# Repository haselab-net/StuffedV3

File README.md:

# Stuffed toy robot version 3 (Starts from 2017) 

* This repository contains Motor driver boards'schematics / PCB layouts, their firmwares and PC software.
* See the wiki (http://git.haselab.net/hasevr/StuffedV3/wikis/home) also.

## Folder structure
- __PIC__ Firmware for pic. WROOM with motor driver also use part of this code.
- __WROOM__ Firmware for WROOM.
- __PCRobokey__ Windows software to control the robot.

# Architecture
WROOM: The main board. One robot has one board.
PIC: Motor driver extension board. Upto eight PIC boards share one UART to communicate with the main WROOM board.

# PIC
## Compiler
MPLABXIDE and XC32 compiler are needed. Install latest of both. Free vesion is enough.
- http://www.microchip.com/mplab/mplab-x-ide see download tab
- http://www.microchip.com/mplab/compilers see download tab

## Setting Macros in the source code.
There are some kinds of boards using the same firmware. So please define appropriate macro for your board.
 See __PIC/boardType.h__ and choose appropriate macro.
In addition, each board sharing the same UART should have different IDs. The ID must be 0 to 7.

# WROOM
 Haoyan Li made a development environment and tutorial.
 See https://github.com/VirgiliaBeatrice/esp32-devenv-vscode and install it.

# PCRobokey
Visual Studio 2015 (14) is used to build. Newer will also work.

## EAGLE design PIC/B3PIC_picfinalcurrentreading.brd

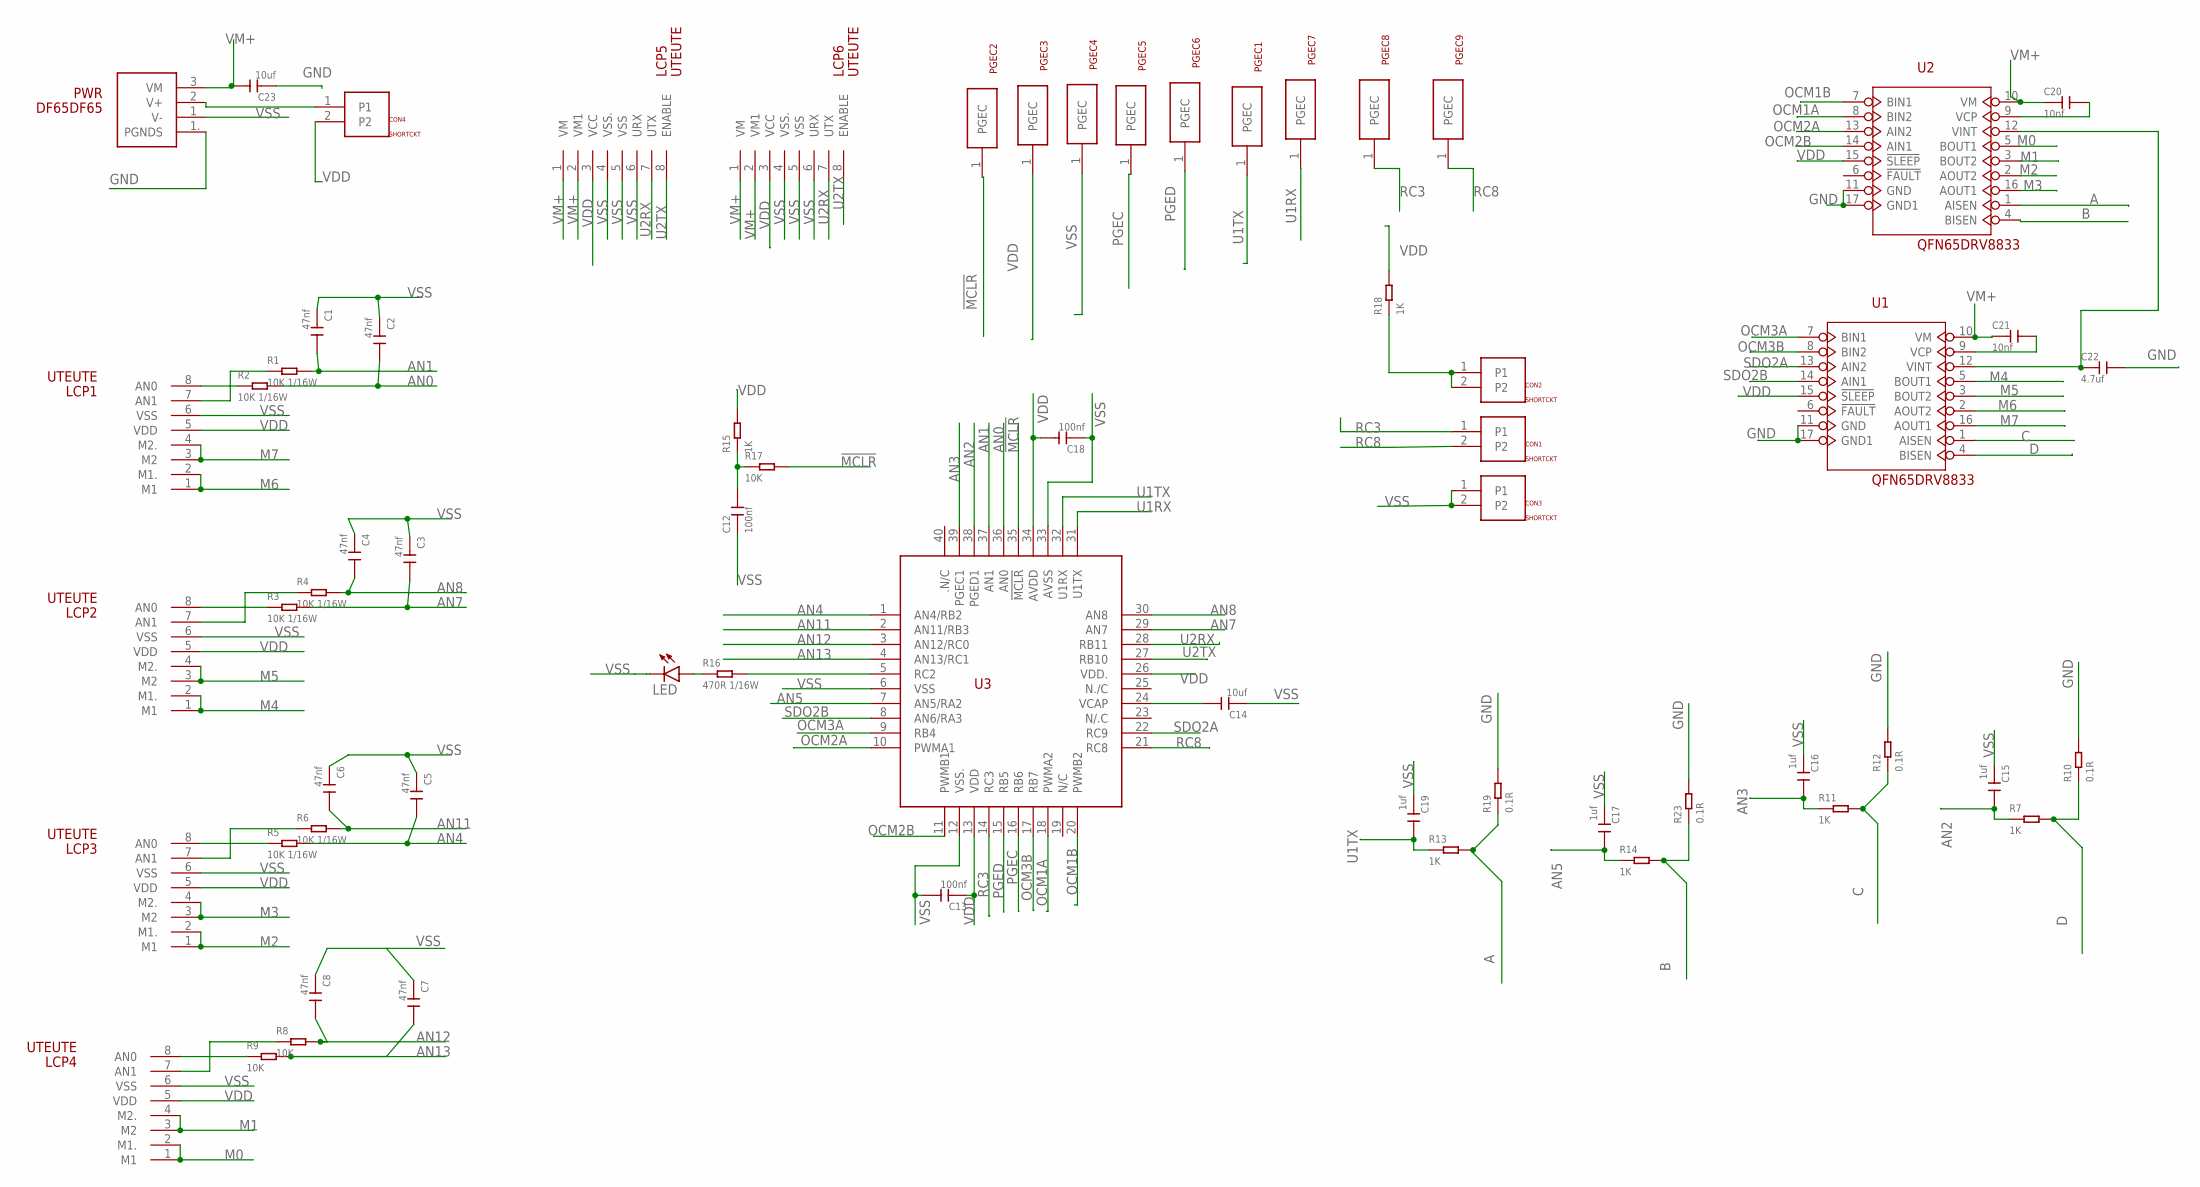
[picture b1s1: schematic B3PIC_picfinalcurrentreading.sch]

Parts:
C1, C2, C3, C4, C5, C6, C7, C8: 47nf; C0402
C12, C13, C18: 100nf; C0402
C14, C23: 10uf; C0402
C15, C16, C17, C19: 1uf; C0402
C20, C21: 10nf; C0402
C22: 4.7uf; C0402
CON1, CON2, CON3, CON4: SHORTCKT; SHORT
LCP1, LCP2, LCP3, LCP4, LCP5, LCP6: UTEUTE; UTE
LED: LEDCHIP-LED0603; CHIP-LED0603
PGEC1, PGEC2, PGEC3, PGEC4, PGEC5, PGEC6, PGEC7, PGEC8, PGEC9: PGECPGEC; PGEC
PWR: DF65DF65; DF65
R1, R2, R3, R4, R5, R6: 10K 1/16W; R0402
R7, R11, R13, R14, R15, R18: 1K; R0402
R8, R9, R17: 10K; R0402
R10, R12, R19, R23: 0.1R; R0805
R16: 470R 1/16W; R0402
U1, U2: QFN65DRV8833; QFN65P400X400X80-17N
U3: PIC32MM0064GPL036PIC32MM0064GPL36; UQFN40MV5X5MM

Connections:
!MCLR!: PGEC2.1, R17.2, U3.35 (!MCLR!)
A: R13.2, R19.1, U2.1 (AISEN)
AN0: C2.2, R2.2, U3.36 (AN0)
AN1: C1.2, R1.2, U3.37 (AN1)
AN2: C15.2, R7.1, U3.38 (PGED1)
AN3: C16.2, R11.1, U3.39 (PGEC1)
AN4: C5.2, R5.2, U3.1 (AN4/RB2)
AN5: C17.2, R14.1, U3.7 (AN5/RA2)
AN7: C3.2, R3.2, U3.29 (AN7)
AN8: C4.2, R4.2, U3.30 (AN8)
AN11: C6.2, R6.2, U3.2 (AN11/RB3)
AN12: C8.2, R8.2, U3.3 (AN12/RC0)
AN13: C7.2, R9.2, U3.4 (AN13/RC1)
B: R14.2, R23.1, U2.4 (BISEN)
C: R11.2, R12.1, U1.1 (AISEN)
D: R7.2, R10.1, U1.4 (BISEN)
GND: C22.2, C23.1, PWR.1. (PGNDS), R10.2, R12.2, R19.2, R23.2, U1.11 (GND), U1.17 (GND1), U2.11 (GND), U2.17 (GND1)
M0: LCP4.1 (M1), LCP4.2 (M1.), U2.5 (BOUT1)
M1: LCP4.3 (M2), LCP4.4 (M2.), U2.3 (BOUT2)
M2: LCP3.1 (M1), LCP3.2 (M1.), U2.2 (AOUT2)
M3: LCP3.3 (M2), LCP3.4 (M2.), U2.16 (AOUT1)
M4: LCP2.1 (M1), LCP2.2 (M1.), U1.5 (BOUT1)
M5: LCP2.3 (M2), LCP2.4 (M2.), U1.3 (BOUT2)
M6: LCP1.1 (M1), LCP1.2 (M1.), U1.2 (AOUT2)
M7: LCP1.3 (M2), LCP1.4 (M2.), U1.16 (AOUT1)
unnamed: LCP1.8 (AN0), R2.1
unnamed: CON4.1, PWR.2 (V+)
unnamed: LCP3.7 (AN1), R6.1
unnamed: LCP2.8 (AN0), R3.1
unnamed: LCP4.7 (AN1), R8.1
unnamed: LCP3.8 (AN0), R5.1
unnamed: LCP2.7 (AN1), R4.1
unnamed: LCP1.7 (AN1), R1.1
unnamed: C12.2, R15.1, R17.1
unnamed: R16.2, U3.5 (RC2)
unnamed: LED.A, R16.1
unnamed: CON2.1, CON2.2, R18.1
unnamed: LCP4.8 (AN0), R9.1
unnamed: C20.2, U2.9 (VCP)
unnamed: C21.2, U1.9 (VCP)
unnamed: C22.1, U1.12 (VINT), U2.12 (VINT)
unnamed: C14.2, U3.24 (VCAP)
OCM1A: U2.8 (BIN2), U3.18 (PWMA2)
OCM1B: U2.7 (BIN1), U3.20 (PWMB2)
OCM2A: U2.13 (AIN2), U3.10 (PWMA1)
OCM2B: U2.14 (AIN1), U3.11 (PWMB1)
OCM3A: U1.7 (BIN1), U3.9 (RB4)
OCM3B: U1.8 (BIN2), U3.17 (RB7)
PGEC: PGEC5.1, U3.16 (RB6)
PGED: PGEC6.1, U3.15 (RB5)
RC3: CON1.1, PGEC8.1, U3.14 (RC3)
RC8: CON1.2, PGEC9.1, U3.21 (RC8)
SDO2A: U1.13 (AIN2), U3.22 (RC9)
SDO2B: U1.14 (AIN1), U3.8 (AN6/RA3)
U1RX: PGEC7.1, U3.31 (U1TX)
U1TX: C19.2, PGEC1.1, R13.1, U3.32 (U1RX)
U2RX: LCP5.7 (UTX), LCP6.7 (UTX), U3.28 (RB11)
U2TX: LCP5.8 (ENABLE), LCP6.8 (ENABLE), U3.27 (RB10)
VDD: C13.1, C18.2, CON4.2, LCP1.5 (VDD), LCP2.5 (VDD), LCP3.5 (VDD), LCP4.5 (VDD), LCP5.3 (VCC), LCP6.3 (VCC), PGEC3.1, R15.2, R18.2, U1.15 (!SLEEP!), U2.15 (!SLEEP!), U3.13 (VDD), U3.26 (VDD.), U3.34 (AVDD)
VM+: C20.1, C21.1, C23.2, LCP5.1 (VM), LCP5.2 (VM1), LCP6.1 (VM), LCP6.2 (VM1), PWR.3 (VM), U1.10 (VM), U2.10 (VM)
VSS: C1.1, C2.1, C3.1, C4.1, C5.1, C6.1, C7.1, C8.1, C12.1, C13.2, C14.1, C15.1, C16.1, C17.1, C18.1, C19.1, CON3.1, CON3.2, LCP1.6 (VSS), LCP2.6 (VSS), LCP3.6 (VSS), LCP4.6 (VSS), LCP5.4 (VSS.), LCP5.5 (VSS), LCP5.6 (URX), LCP6.4 (VSS.), LCP6.5 (VSS), LCP6.6 (URX), LED.C, PGEC4.1, PWR.1 (V-), U3.6 (VSS), U3.12 (VSS.), U3.33 (AVSS)

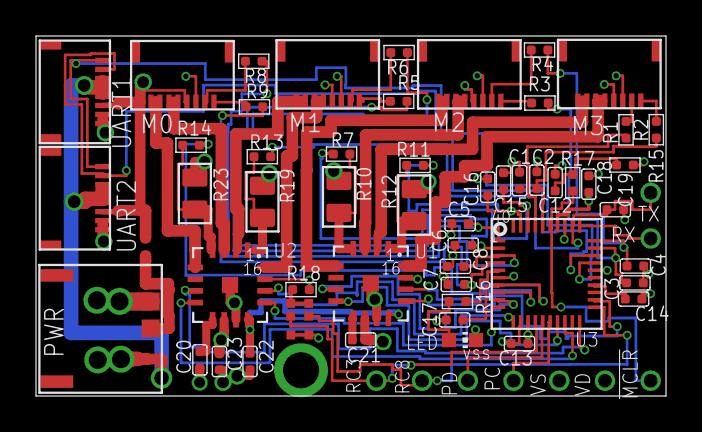
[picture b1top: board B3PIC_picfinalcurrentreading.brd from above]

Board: 4 copper layers, 35.0 x 20.0 mm, 64 parts (0 on the bottom side), 61 nets.

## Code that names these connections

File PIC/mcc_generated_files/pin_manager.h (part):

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#define channel_AN1_SetDigitalOutput()   ( TRISACLR = (1 << 1) )
/**
  @Summary
    Sets the GPIO pin, RA2, high using LATAbits.LATA2.

  @Description
    Sets the GPIO pin, RA2, high using LATAbits.LATA2.

  @Preconditions
    The RA2 must be set to an output.
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#define IO_RA2_SetHigh()          ( LATASET = (1 << 2) )
/**
  @Summary
    Sets the GPIO pin, RA2, low using LATAbits.LATA2.

  @Description
    Sets the GPIO pin, RA2, low using LATAbits.LATA2.

  @Preconditions
    The RA2 must be set to an output.
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    Sets a value to the GPIO pin.

  @Description
    Sets or Resets the GPIO pin, RA2, low or high using LATAbits.LATA2.

  @Preconditions
    The RA2 must be set to an output.
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
/**
  @Summary
    Toggles the GPIO pin, RA2, using LATAbits.LATA2.

  @Description
    Toggles the GPIO pin, RA2, using LATAbits.LATA2.

  @Preconditions
    The RA2 must be set to an output.
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#define IO_RA2_Toggle()           ( LATAINV = (1 << 2) )
/**
  @Summary
    Reads the value of the GPIO pin, RA2.

  @Description
    Reads the value of the GPIO pin, RA2.

  @Preconditions
    None.
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    </code>

*/
#define IO_RA2_GetValue()         PORTAbits.RA2
/**
  @Summary
    Configures the GPIO pin, RA2, as an input.

  @Description
    Configures the GPIO pin, RA2, as an input.

  @Preconditions
    None.
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#define IO_RA2_SetDigitalInput()   ( TRISASET = (1 << 2) )
/**
  @Summary
    Configures the GPIO pin, RA2, as an output.

  @Description
    Configures the GPIO pin, RA2, as an output.

  @Preconditions
    None.
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#define IO_RA2_SetDigitalOutput()   ( TRISACLR = (1 << 2) )
/**
  @Summary
    Sets the GPIO pin, RB10, high using LATBbits.LATB10.

  @Description
    Sets the GPIO pin, RB10, high using LATBbits.LATB10.

  @Preconditions
    The RB10 must be set to an output.
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#define IO_RB10_SetHigh()          ( LATBSET = (1 << 10) )
/**
  @Summary
    Sets the GPIO pin, RB10, low using LATBbits.LATB10.

  @Description
    Sets the GPIO pin, RB10, low using LATBbits.LATB10.

  @Preconditions
    The RB10 must be set to an output.
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    Sets a value to the GPIO pin.

  @Description
    Sets or Resets the GPIO pin, RB10, low or high using LATBbits.LATB10.

  @Preconditions
    The RB10 must be set to an output.
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
/**
  @Summary
    Toggles the GPIO pin, RB10, using LATBbits.LATB10.

  @Description
    Toggles the GPIO pin, RB10, using LATBbits.LATB10.

  @Preconditions
    The RB10 must be set to an output.
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#define IO_RB10_Toggle()           ( LATBINV = (1 << 10) )
/**
  @Summary
    Reads the value of the GPIO pin, RB10.

  @Description
    Reads the value of the GPIO pin, RB10.

  @Preconditions
    None.
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    </code>

*/
#define IO_RB10_GetValue()         PORTBbits.RB10
/**
  @Summary
    Configures the GPIO pin, RB10, as an input.

  @Description
    Configures the GPIO pin, RB10, as an input.

  @Preconditions
    None.
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#define IO_RB10_SetDigitalInput()   ( TRISBSET = (1 << 10) )
/**
  @Summary
    Configures the GPIO pin, RB10, as an output.

  @Description
    Configures the GPIO pin, RB10, as an output.

  @Preconditions
    None.
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#define IO_RB10_SetDigitalOutput()   ( TRISBCLR = (1 << 10) )
/**
  @Summary
    Sets the GPIO pin, RB11, high using LATBbits.LATB11.

  @Description
    Sets the GPIO pin, RB11, high using LATBbits.LATB11.

  @Preconditions
    The RB11 must be set to an output.
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#define IO_RB11_SetHigh()          ( LATBSET = (1 << 11) )
/**
  @Summary
    Sets the GPIO pin, RB11, low using LATBbits.LATB11.

  @Description
    Sets the GPIO pin, RB11, low using LATBbits.LATB11.

  @Preconditions
    The RB11 must be set to an output.
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    Sets a value to the GPIO pin.

  @Description
    Sets or Resets the GPIO pin, RB11, low or high using LATBbits.LATB11.

  @Preconditions
    The RB11 must be set to an output.
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
/**
  @Summary
    Toggles the GPIO pin, RB11, using LATBbits.LATB11.

  @Description
    Toggles the GPIO pin, RB11, using LATBbits.LATB11.

  @Preconditions
    The RB11 must be set to an output.
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#define IO_RB11_Toggle()           ( LATBINV = (1 << 11) )
/**
  @Summary
    Reads the value of the GPIO pin, RB11.

  @Description
    Reads the value of the GPIO pin, RB11.

  @Preconditions
    None.
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    </code>

*/
#define IO_RB11_GetValue()         PORTBbits.RB11
/**
  @Summary
    Configures the GPIO pin, RB11, as an input.

  @Description
    Configures the GPIO pin, RB11, as an input.

  @Preconditions
    None.
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#define IO_RB11_SetDigitalInput()   ( TRISBSET = (1 << 11) )
/**
  @Summary
    Configures the GPIO pin, RB11, as an output.

  @Description
    Configures the GPIO pin, RB11, as an output.

  @Preconditions
    None.
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#define IO_RB14_SetDigitalOutput()   ( TRISBCLR = (1 << 14) )
/**
  @Summary
    Sets the GPIO pin, RB2, high using LATBbits.LATB2.

  @Description
    Sets the GPIO pin, RB2, high using LATBbits.LATB2.

  @Preconditions
    The RB2 must be set to an output.
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#define channel_AN4_SetHigh()          ( LATBSET = (1 << 2) )
/**
  @Summary
    Sets the GPIO pin, RB2, low using LATBbits.LATB2.

  @Description
    Sets the GPIO pin, RB2, low using LATBbits.LATB2.

  @Preconditions
    The RB2 must be set to an output.
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    Sets a value to the GPIO pin.

  @Description
    Sets or Resets the GPIO pin, RB2, low or high using LATBbits.LATB2.

  @Preconditions
    The RB2 must be set to an output.
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
/**
  @Summary
    Toggles the GPIO pin, RB2, using LATBbits.LATB2.

  @Description
    Toggles the GPIO pin, RB2, using LATBbits.LATB2.

  @Preconditions
    The RB2 must be set to an output.
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#define channel_AN4_Toggle()           ( LATBINV = (1 << 2) )
/**
  @Summary
    Reads the value of the GPIO pin, RB2.

  @Description
    Reads the value of the GPIO pin, RB2.

  @Preconditions
    None.
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    </code>

*/
#define channel_AN4_GetValue()         PORTBbits.RB2
/**
  @Summary
    Configures the GPIO pin, RB2, as an input.

  @Description
    Configures the GPIO pin, RB2, as an input.

  @Preconditions
    None.
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#define channel_AN4_SetDigitalInput()   ( TRISBSET = (1 << 2) )
/**
  @Summary
    Configures the GPIO pin, RB2, as an output.

  @Description
    Configures the GPIO pin, RB2, as an output.

  @Preconditions
    None.
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#define channel_AN4_SetDigitalOutput()   ( TRISBCLR = (1 << 2) )
/**
  @Summary
    Sets the GPIO pin, RB3, high using LATBbits.LATB3.

  @Description
    Sets the GPIO pin, RB3, high using LATBbits.LATB3.

  @Preconditions
    The RB3 must be set to an output.
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#define channel_AN11_SetHigh()          ( LATBSET = (1 << 3) )
/**
  @Summary
    Sets the GPIO pin, RB3, low using LATBbits.LATB3.

  @Description
    Sets the GPIO pin, RB3, low using LATBbits.LATB3.

  @Preconditions
    The RB3 must be set to an output.
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    Sets a value to the GPIO pin.

  @Description
    Sets or Resets the GPIO pin, RB3, low or high using LATBbits.LATB3.

  @Preconditions
    The RB3 must be set to an output.
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
/**
  @Summary
    Toggles the GPIO pin, RB3, using LATBbits.LATB3.

  @Description
    Toggles the GPIO pin, RB3, using LATBbits.LATB3.

  @Preconditions
    The RB3 must be set to an output.
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#define channel_AN11_Toggle()           ( LATBINV = (1 << 3) )
/**
  @Summary
    Reads the value of the GPIO pin, RB3.

  @Description
    Reads the value of the GPIO pin, RB3.

  @Preconditions
    None.
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    </code>

*/
#define channel_AN11_GetValue()         PORTBbits.RB3
/**
  @Summary
    Configures the GPIO pin, RB3, as an input.

  @Description
    Configures the GPIO pin, RB3, as an input.

  @Preconditions
    None.
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#define channel_AN11_SetDigitalInput()   ( TRISBSET = (1 << 3) )
/**
  @Summary
    Configures the GPIO pin, RB3, as an output.

  @Description
    Configures the GPIO pin, RB3, as an output.

  @Preconditions
    None.
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#define channel_AN11_SetDigitalOutput()   ( TRISBCLR = (1 << 3) )
/**
  @Summary
    Sets the GPIO pin, RB5, high using LATBbits.LATB5.

  @Description
    Sets the GPIO pin, RB5, high using LATBbits.LATB5.

  @Preconditions
    The RB5 must be set to an output.
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#define IO_RB5_SetHigh()          ( LATBSET = (1 << 5) )
/**
  @Summary
    Sets the GPIO pin, RB5, low using LATBbits.LATB5.

  @Description
    Sets the GPIO pin, RB5, low using LATBbits.LATB5.

  @Preconditions
    The RB5 must be set to an output.
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    Sets a value to the GPIO pin.

  @Description
    Sets or Resets the GPIO pin, RB5, low or high using LATBbits.LATB5.

  @Preconditions
    The RB5 must be set to an output.
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
/**
  @Summary
    Toggles the GPIO pin, RB5, using LATBbits.LATB5.

  @Description
    Toggles the GPIO pin, RB5, using LATBbits.LATB5.

  @Preconditions
    The RB5 must be set to an output.
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#define IO_RB5_Toggle()           ( LATBINV = (1 << 5) )
/**
  @Summary
    Reads the value of the GPIO pin, RB5.

  @Description
    Reads the value of the GPIO pin, RB5.

  @Preconditions
    None.
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    </code>

*/
#define IO_RB5_GetValue()         PORTBbits.RB5
/**
  @Summary
    Configures the GPIO pin, RB5, as an input.

  @Description
    Configures the GPIO pin, RB5, as an input.

  @Preconditions
    None.
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#define IO_RB5_SetDigitalInput()   ( TRISBSET = (1 << 5) )
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
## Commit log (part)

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2019-05-27 Support for all board(BOARD0 to BOARD4).
2019-05-28 Support for all board (BOARD0 to BOARD4)
2019-05-28 fix espfs
2019-05-30 Improve wifi and wifi AP setting forms.
2019-06-04 Update sr_motor.js
    for better movement see issue 3 in pxt
2019-06-10 Update sr_motor.js
    remove multi spaces in movment codestr
2019-06-11 Update sr_softrobot.js
    clear send queue and reset interpolate parameters after send direct
2019-06-14 ping pong for websocket
2019-06-27 fix block_pause
2019-06-27 ifttt support
2019-06-28 change gitignore
2019-07-01 finish mqtt client
2019-07-04 enable trigger webhook
2019-07-12 multi thread test
2019-07-12 (WIP) compiled but not tested
2019-07-13 fix tick
2019-07-13 (WIP) add UDP interface
2019-07-13 fix forever dropNextKeyframe when start
2019-07-13 Send PIC interpolate command in fixed short interval
    Still remains problem:
    1. PIC buffer some times overflows
    2. the pose is not correct
2019-07-13 deal with overflow on PIC interpolate buffer
2019-07-13 fix movementQueryInterpolateState
2019-07-13 Pause function of JS is fixed. Only two threads for Duktape.
2019-07-15 add duktape function for adding keyframe
2019-07-16 Add debug function DUK_STACK_REMAIN to print remaining stack size. Some modification to stop developing codes.
2019-07-16 increment target write when target read shift
2019-07-16 fix wrong return packet of CIU_MOVEMENT?
2019-07-16 full CIU_MOVEMENT support on softRobot side
2019-07-16 finish duktape c lib for movement control
2019-07-17 duktape CIU_MOVEMENT support
2019-07-17 Reduce stack usage in JS tasks.
2019-07-18 some fix
2019-07-18 add support for changing control mode
2019-07-18 fix little endian bug
2019-07-19 back to former UdpCom
2019-07-19 new movement js lib
2019-07-19 clear js lib
2019-07-19 do not load iot
    IoT prevent ws connection when JS is running
2019-07-20 fix memory leak
2019-07-20 Enable main.js
2019-07-20 OldOne
2019-07-20 Fixed lost block during changing to reduce stack usage.
2019-07-20 JS enbug fixed. Use debug compile option. Stack check by pointer.
2019-07-20 assertion in duktape makes huge code. So under assertion.
2019-07-20 JS stack size was too small.
2019-07-21 add handler for timer(bug: memory becomes not enougth after several callbacks)
2019-07-22 let event handler handle forever loop
2019-07-22 Add monitor command to call js function.
2019-07-23 new main,js
2019-07-23 fix bug in pause movement
2019-07-23 Just merged
2019-07-23 JS for timerTest added. use it instead of runtime.js
2019-07-24 fix bug on dead lock caused by call event when processing event in clearInterpolateBuffer
2019-07-24 fix another dead lock problem
2019-07-24 memory leak test
2019-07-24 query interpolate state after change control mode
2019-07-24 fix memory leak caused by bind(this) in setTimeout
2019-07-24 replace timeout with interval in movementSender
2019-07-24 fix memory leak on iot, and reduce memory usage for mqtt task
2019-07-24 add call stack dump to ESP32
2019-07-24 Fix memory leak when duktape ends.
2019-07-25 fix bug: long time pause
2019-07-25 Remove print_stack
2019-07-25 Add isQuitting
2019-07-25 Add code for during quitting.
2019-07-25 Change priorities of tasks.
2019-07-25 memory not enough
2019-07-25 move touch callback to C++
2019-07-25 remove unused callbacks
2019-07-25 remove timer wrapper.
2019-07-25 simplify js callback code
2019-07-25 move CI_DIRECT and CI_SETPARAM to C++
2019-07-26 fix callbacks js lib error
2019-07-26 init.js runs in a temp task.
2019-07-26 fix error in js lib
2019-07-26 fix movementSender
2019-07-26 simplify the process of loading js movement lib
2019-07-26 move main to init.js
2019-07-28 setInterval stuck
2019-07-29 Fix js timer not to call after erasing the event queue.
2019-07-30 bettet switch between control modes of movement
2019-07-30 change html url parameter
2019-07-30 add iot functions
2019-07-31 Add heat limit
2019-07-31 fix typo
2019-07-31 shorter interval for sensor query
2019-07-31 send firmware version to pxt
2019-07-31 resume movement after stop JS task
2019-07-31 Now, torque limit by heat starts from 1/4 of the heat limit.
2019-07-31 finish nvs support
2019-07-31 add offline_mode to nvs
2019-07-31 change to auto_start
2019-07-31 Fix WiFi forms
2019-08-01 Fixed for robokey.
2019-08-01 Fix mistake not to start Movement
2019-08-01 fix play movementDecoder memory leak bug
2019-08-01 Add delay to avoid instability of start up of ADC conversion.
2019-08-01 Adjust center value of rotation sensor for recent hardware.
2019-08-02 error running main.js
2019-08-02 Fix start up motion problem.
2019-08-05 update FIRMWARE_VERSION
2019-08-06 fix bug in resume movement (not all movement resumed)
2019-08-07 fix bug of minus wrong nOccupied
2019-08-08 fix monitor and read motorPos
2019-08-08 set local storage of pose in duktape to int32_t
2019-08-13 Fix motor position reset.
2019-08-18 Fix call of duktape_end() not to block PINGPONG of web socket.
2019-08-21 inform pxt when create / delete jsfile task success
2019-08-26 new return packet for CI_M_QUERY
2019-08-26 fix compile error and add print function for monitor
2019-08-26 esp32 support for new movement sender
2019-08-26 add js api isMovementPlaying
2019-08-30 new command rule
2019-08-30 fix bugs
2019-08-30 fix bug
    bug:
    the nextTime is not updated
2019-08-30 add support for play after, and increase js task size
2019-09-02 check movement state before pause / resume movement
2019-09-02 add support for block to check movement state
2019-09-06 fix add keyframe with ref
2019-09-06 timeOffset should in movement tick time space
2019-09-06 fix min time
2019-09-07 add keyframe in default when ref failed
2019-09-07 use strict mode in adding keyframe
2019-09-08 not use strict mode for play after
2019-09-09 fix sr_motor.js
2019-09-09 fix return packet length
2019-09-22 round time when converting from ms to movement tick
2019-09-24 update version
2019-09-29 do not respond form in low heap status
2019-10-07 release version
2019-10-07 revert to test version
2019-10-21 enable core dump and disable gdb in sdkconfig
2019-10-24 could download ota updater in WROOM
2019-10-24 add OTA updater (WIP)
2019-10-24 update ota server address
2019-10-24 update ota updater sdkconfig
2019-10-24 switch to cpp
2019-10-24 update certificate
2019-10-24 allow update ota from pxt ws message
2019-10-24 set to 0 before set http config
2019-10-24 update config
2019-10-24 extend partition for ota updater
2019-11-07 Add ld file
2019-11-12 Fix bug when more than two boards are connected.
2019-11-12 add variable to record movement count
2019-11-12 fix movementCount
2019-11-12 add support for two JS api: 1. getDuration, 2. remainingCount
2019-11-16 Add set motor heat function.
2019-11-16 copy source instead of symlink
2019-11-18 change play with / after block expression
2019-11-18 allow print number in esp
2019-11-18 fix bug on decrease movement count
2019-11-18 Fix motor heat calculation to avoid overflow.
2019-11-26 Add CI_GETPARAM. Move CIU commands to start from 32.
2019-11-26 fix bug that on end is not triggered
2019-11-26 update firmware version
2019-11-28 Fix for CI_GETPARAM (add command and return length)
2019-11-29 define PDPARAM_K B A as initial values of motor parameters.
2019-12-02 CI_GETPARAM works.
2019-12-02 Fix some code (has no effect to the function)
2019-12-02 Fix SAVE_ALLMOTORPARAM_ON_WROOM option.
2019-12-05 type of heatLimit is changed. LDEC -> long and transmit it in 16 bits by dividing it by HeatRelease Fix command len in PCController
2019-12-07 Fix CI_GET_PARAMTER and problem caused by initialization of PCRobokey.
2019-12-07 Fix PCController Add some comments and refactoring on WROOM.
2019-12-08 Fixed interpolation of PCRobokey. The sudden stop problem is fixed.
2019-12-13 Add Haptic (Virtual wall and vibration) function.
2019-12-14 fix bug of not working properly with CI_DIRECT in sync mode
2019-12-14 fix wrong command movement id
2019-12-14 update version number
2019-12-15 replaceFSImage() (write *.img file to replace content of the whole file system) is added. Fix sum dirty code of PCController.
2020-01-17 Fix for Springhead
2020-01-17 Fix include path
2020-01-23 Add error message for invalid command for board.h Add haptic feedback test in PCController
2020-01-27 update firmware version to release
2020-01-28 clear flash before update
2020-02-10 increase firmware version
2020-03-24 Add deep sleep test in monitor.cpp
2020-03-25 add ulp run to monitor
2020-03-26 Add ADC initialization checking code.
2020-04-26 add NVMWrite test
2020-05-20 PCController Failed to add Magnet Sensor Panel source.
2020-05-20 Forgot to add
2020-05-21 Prevent strong current when switch on motor power during current control mode.
2020-05-23 PIC: Add dead band for current control of all four motors.
2020-05-23 PCController: Load default function on HeatLimit and HeatRelease Fix comments on PIC/control.c
2020-05-23 WROOM: After brownout reset, motor torque limit is set to 0 to stop servo to prevent brownout again and again.
2020-06-02 Change spidar's default PD Value
2021-03-13 Initial commit for V4.2
2021-03-24 Try to fix lwip_recv_r to lwip_recv problem. But not finished.
2021-03-24 Fix: Add mutex to Socket, SetLength() of CIU_MOVEMENT command. Seems to work well.
2021-03-25 Change motor power to prevent reset by changing pwm limit when brownout.
2021-04-03 PIC: Change parameter for SPIDAR's default.
2021-04-03 PIC: Fix codes for new compiler
2021-07-16 Fix: Auto Calibrate magnetic sensor's amplitude and offset.
2021-08-03 Feat: Current command returns forces instead of currents.
2021-08-11 Fix: compile error due to update of PIC firmware.
2021-09-16 Fix: extern "C" was needed to include C header from C++.
2021-09-16 remove unnecessary files.
2021-10-14 Fix: Force sensor value should not be scaled.
2021-11-29 Remove unused files. Fix binary semaphore
2021-11-30 Fit for v3.3.5
2021-12-03 Fit to v4.3.1. before remove WiFi of espsnippets.
2021-12-04 Fix: Some binary semaphores are not given. Remove WiFi.cpp and use latest WiFi API.
2021-12-04 Fix: Rename file. Use logging.h instead of esp_log.h.
2021-12-04 Fix: IP address for AP. Ask to browser to reload when no more process exception occurs.
2021-12-06 Fix: remove abort() when wifi connection fails.
2022-01-15 Update .gitignore and sdkconfig.
2022-02-18 Add PICMK files. Still modifying.
2022-02-18 Add codes for 8 motor driver by PIC32MK.
2022-08-11 コロコロのためのモーター制御
2022-08-17 Unityからメッセージを受け取れるようにした
2022-08-18 コメントを追加した
2022-08-30 remove: PCController → Unity
2022-10-01 Feat: PWM for current control and ADC works.
2022-10-19 Feat: UART2 for command works.
2022-10-21 Fix: PWM default value, readADC (for motor angles).
2022-10-24 It works. Fix: Use TMR2 instead of CoreTimer. NVWrite.
2022-11-02 新しいモータードライバーにOSC通信追加
2022-11-07 Fix: PWM setting.
2023-06-30 Fix: NCurrent for PC
2023-08-05 For IVRC 2023: Multi-Threader Project.
2023-08-07 Mainform.cs にてint型をOSCで受け取るように変更
2023-09-05 メッセージアドレス/uOSC/rightで送信されてきたメッセージについてcurrentに格納するように変更
2023-09-06 2台使えるようになりました
2023-11-08 Fix: Update for MPLAB IDE X 6.15.
2023-11-11 Fix: Update for MPLABXIDE 6.15. Finished.
2023-11-11 Feat: Encoder Counter
2023-11-11 Feat: Add set and get parameter command for encoder flags.
2023-11-12 Feat: Send and Receive encoder flags in the Param panel.
2023-11-14 Feat: Quadratic rotary encoder reader for all motors.
2023-12-01 Fix: PWM for motor 8.
2023-12-01 Fix: PWM8's problem solved.
2023-12-06 Fix: CW, CCW, AN5 etc.
2023-12-06 Opti: Exec for return and start to return in one interrupt.
2023-12-06 UART not work well
2023-12-08 Opti: UARTC RX handler.
2023-12-08 Fix: Compile errors on PIC32MM.
2023-12-10 Fix: Remove pwmResolution from CI_BOARD_INFO's packet. (for compatibility).
2023-12-11 Fix: 2,000,000 baud comes to work fine today.
2024-02-21 PICMKでkorokoroを動かすためにOSC通信を出来るようにした。
2024-03-24 Workaround: For some PIC32MK board, 122MHz sys clock is needed for UART.
2024-07-30 Add start button as a trial.
2024-08-16 motor control
2024-11-29 Added numerical calculation formulas
2024-12-04 add formula
2024-12-22 Deletion of commented-out sections add new formula of haptics.currents[2]
2024-12-23 complete formulas of 5 motors
2024-12-24 complete formula

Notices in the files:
PIC/mcc_generated_files/pin_manager.h:
Copyright (c) 2013 - 2015 released Microchip Technology Inc.  All rights reserved.
